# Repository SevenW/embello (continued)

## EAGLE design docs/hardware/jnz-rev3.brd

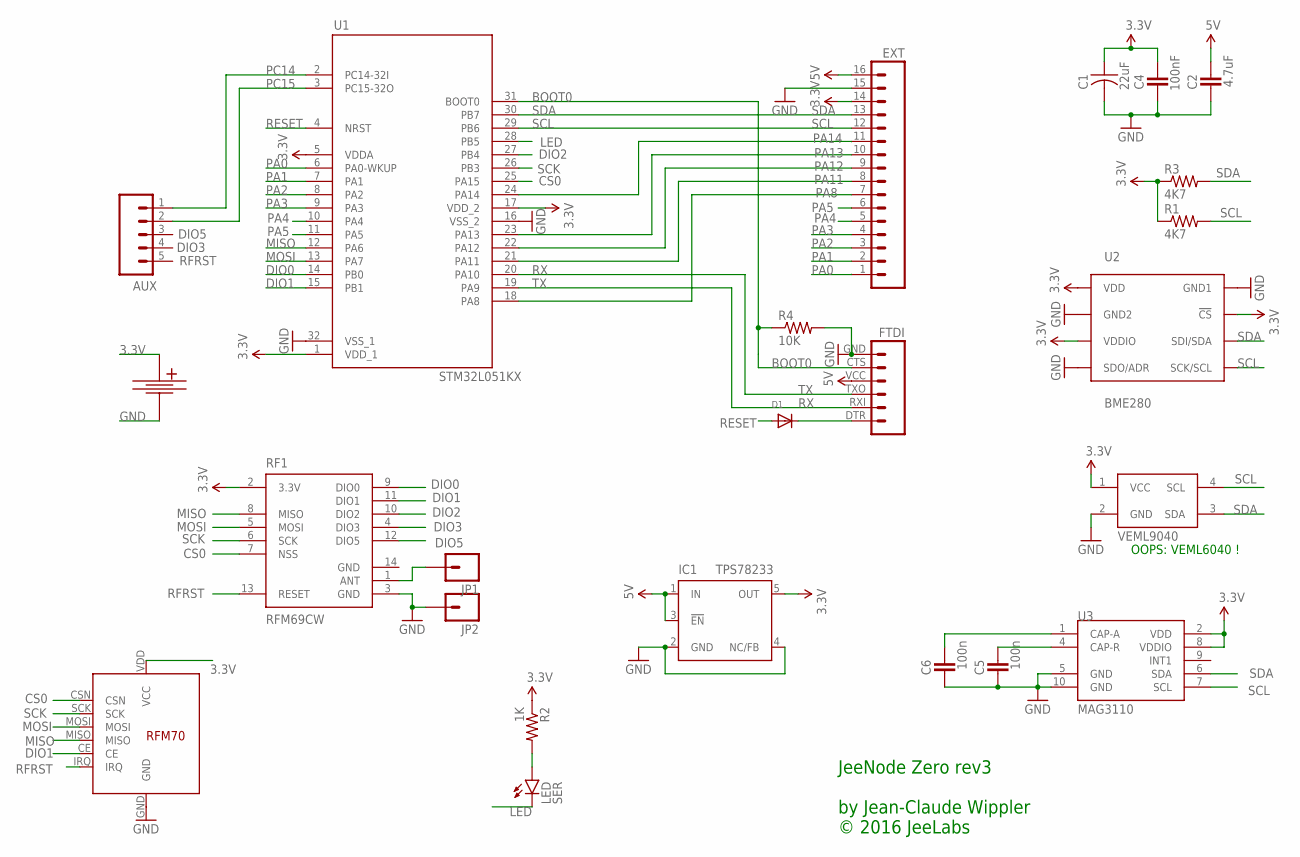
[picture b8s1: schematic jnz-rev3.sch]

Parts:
AUX: M05NO_SILK; 1X05_NO_SILK
C1: 22uF; C0805
C2: 4.7uF; C0805K
C4: 100nF; C0603K
C5, C6: 100n; C0603K
D1: DIODESOD-323F; SOD-323F
EXT: M161X16_NO_SILK; 1X16_NO_SILK
FTDI: FTDI_BASICPTH; FTDI_BASIC
IC1: TPS78233; SOT23-DBV
JP1, JP2: M01NOSILK-KIT; 1X01NS-KIT
LED: SER; LED-0603
R1, R3: 4K7; 0603-RES
R2: 1K; 0603-RES
R4: 10K; 0603-RES
RF1: RFM69CW; RFM69CW-XXXS2
RF2: RFM7x; RFM70
U1: STM32L051KX; TQFP32-08
U2: BME280; BME280_LGA
U3: MAG3110; DFN-10
U$2: CR2032-SMD
U$3: VEML6040; OPLGA-4

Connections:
3.3V: C1.1, C4.1, EXT.14, IC1.5 (OUT), R1.1, R2.1, R3.1, RF1.2 (3.3V), RF2.VDD (VCC), U1.1 (VDD_1), U1.5 (VDDA), U1.17 (VDD_2), U2.P$2 (!CS), U2.P$6 (VDDIO), U2.P$8 (VDD), U3.2 (VDD), U3.8 (VDDIO), U$2.POS (+), U$3.1 (VCC)
5V: C2.1, EXT.16, FTDI.VCC (4), IC1.1 (IN), IC1.3 (!EN)
BOOT0: FTDI.CTS (5), R4.1, U1.31 (BOOT0)
CS0: RF1.7 (NSS), RF2.CSN, U1.25 (PA15)
DIO0: RF1.9 (DIO0), U1.14 (PB0)
DIO1: RF1.11 (DIO1), RF2.CE, U1.15 (PB1)
DIO2: RF1.10 (DIO2), U1.27 (PB4)
DIO3: AUX.4, RF1.4 (DIO3)
DIO5: AUX.3, RF1.12 (DIO5)
GND: C1.2, C2.2, C4.2, C5.2, C6.2, EXT.15, FTDI.GND (6), IC1.2 (GND), IC1.4 (NC/FB), JP2.1, R4.2, RF1.3 (GND), RF1.14 (GND), RF2.GND, U1.16 (VSS_2), U1.32 (VSS_1), U2.P$1 (GND1), U2.P$5 (SDO/ADR), U2.P$7 (GND2), U3.5 (GND), U3.10 (GND), U$2.NEG (-), U$3.2 (GND)
LED: LED.C, U1.28 (PB5)
MISO: RF1.8 (MISO), RF2.MISO, U1.12 (PA6)
MOSI: RF1.5 (MOSI), RF2.MOSI, U1.13 (PA7)
unnamed: D1.C, FTDI.DTR (1)
unnamed: LED.A, R2.2
unnamed: C5.1, U3.4 (CAP-R)
unnamed: C6.1, U3.1 (CAP-A)
unnamed: JP1.1, RF1.1 (ANT)
PA0: EXT.1, U1.6 (PA0-WKUP)
PA1: EXT.2, U1.7 (PA1)
PA2: EXT.3, U1.8 (PA2)
PA3: EXT.4, U1.9 (PA3)
PA4: EXT.5, U1.10 (PA4)
PA5: EXT.6, U1.11 (PA5)
PA8: EXT.7, U1.18 (PA8)
PA11: EXT.8, U1.21 (PA11)
PA12: EXT.9, U1.22 (PA12)
PA13: EXT.10, U1.23 (PA13)
PA14: EXT.11, U1.24 (PA14)
PC14: AUX.1, U1.2 (PC14-32I)
PC15: AUX.2, U1.3 (PC15-32O)
RESET: D1.A, U1.4 (NRST)
RFRST: AUX.5, RF1.13 (RESET), RF2.IRQ
RX: FTDI.TXO (3), U1.20 (PA10)
SCK: RF1.6 (SCK), RF2.SCK, U1.26 (PB3)
SCL: EXT.12, R1.2, U1.29 (PB6), U2.P$4 (SCK/SCL), U3.7 (SCL), U$3.4 (SCL)
SDA: EXT.13, R3.2, U1.30 (PB7), U2.P$3 (SDI/SDA), U3.6 (SDA), U$3.3 (SDA)
TX: FTDI.RXI (2), U1.19 (PA9)

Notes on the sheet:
JeeNode Zero rev3 by Jean-Claude Wippler © 2016 JeeLabs
OOPS: VEML6040 !

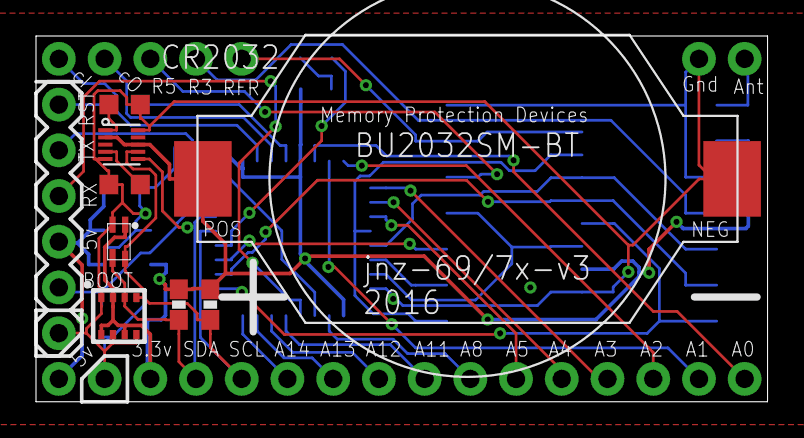
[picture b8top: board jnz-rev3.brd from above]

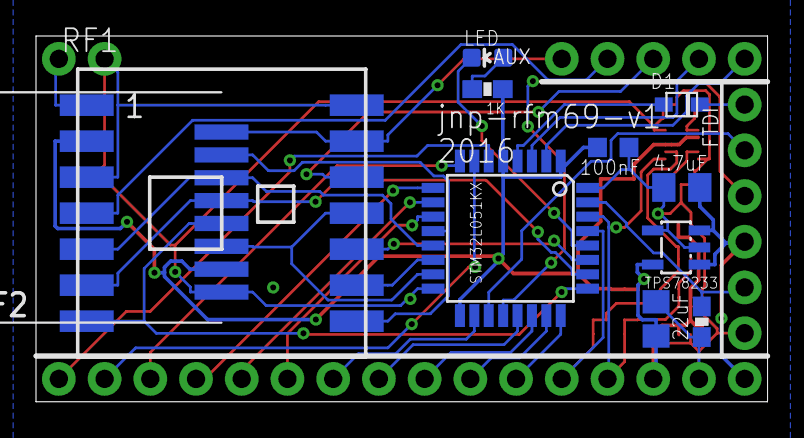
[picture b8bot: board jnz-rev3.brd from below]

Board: 2 copper layers, 40.6 x 20.3 mm, 24 parts (11 on the bottom side), 38 nets.

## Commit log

2017-06-01 fix problem in cmac
2017-06-01 JeeNode Zero LoraWAN for The Things Network in Forth
2017-06-17 catch up
2017-06-17 Revert "catch up"
    This reverts commit 631ed7d8882b8cfee5cdd500fbf6f9913ced4866.
